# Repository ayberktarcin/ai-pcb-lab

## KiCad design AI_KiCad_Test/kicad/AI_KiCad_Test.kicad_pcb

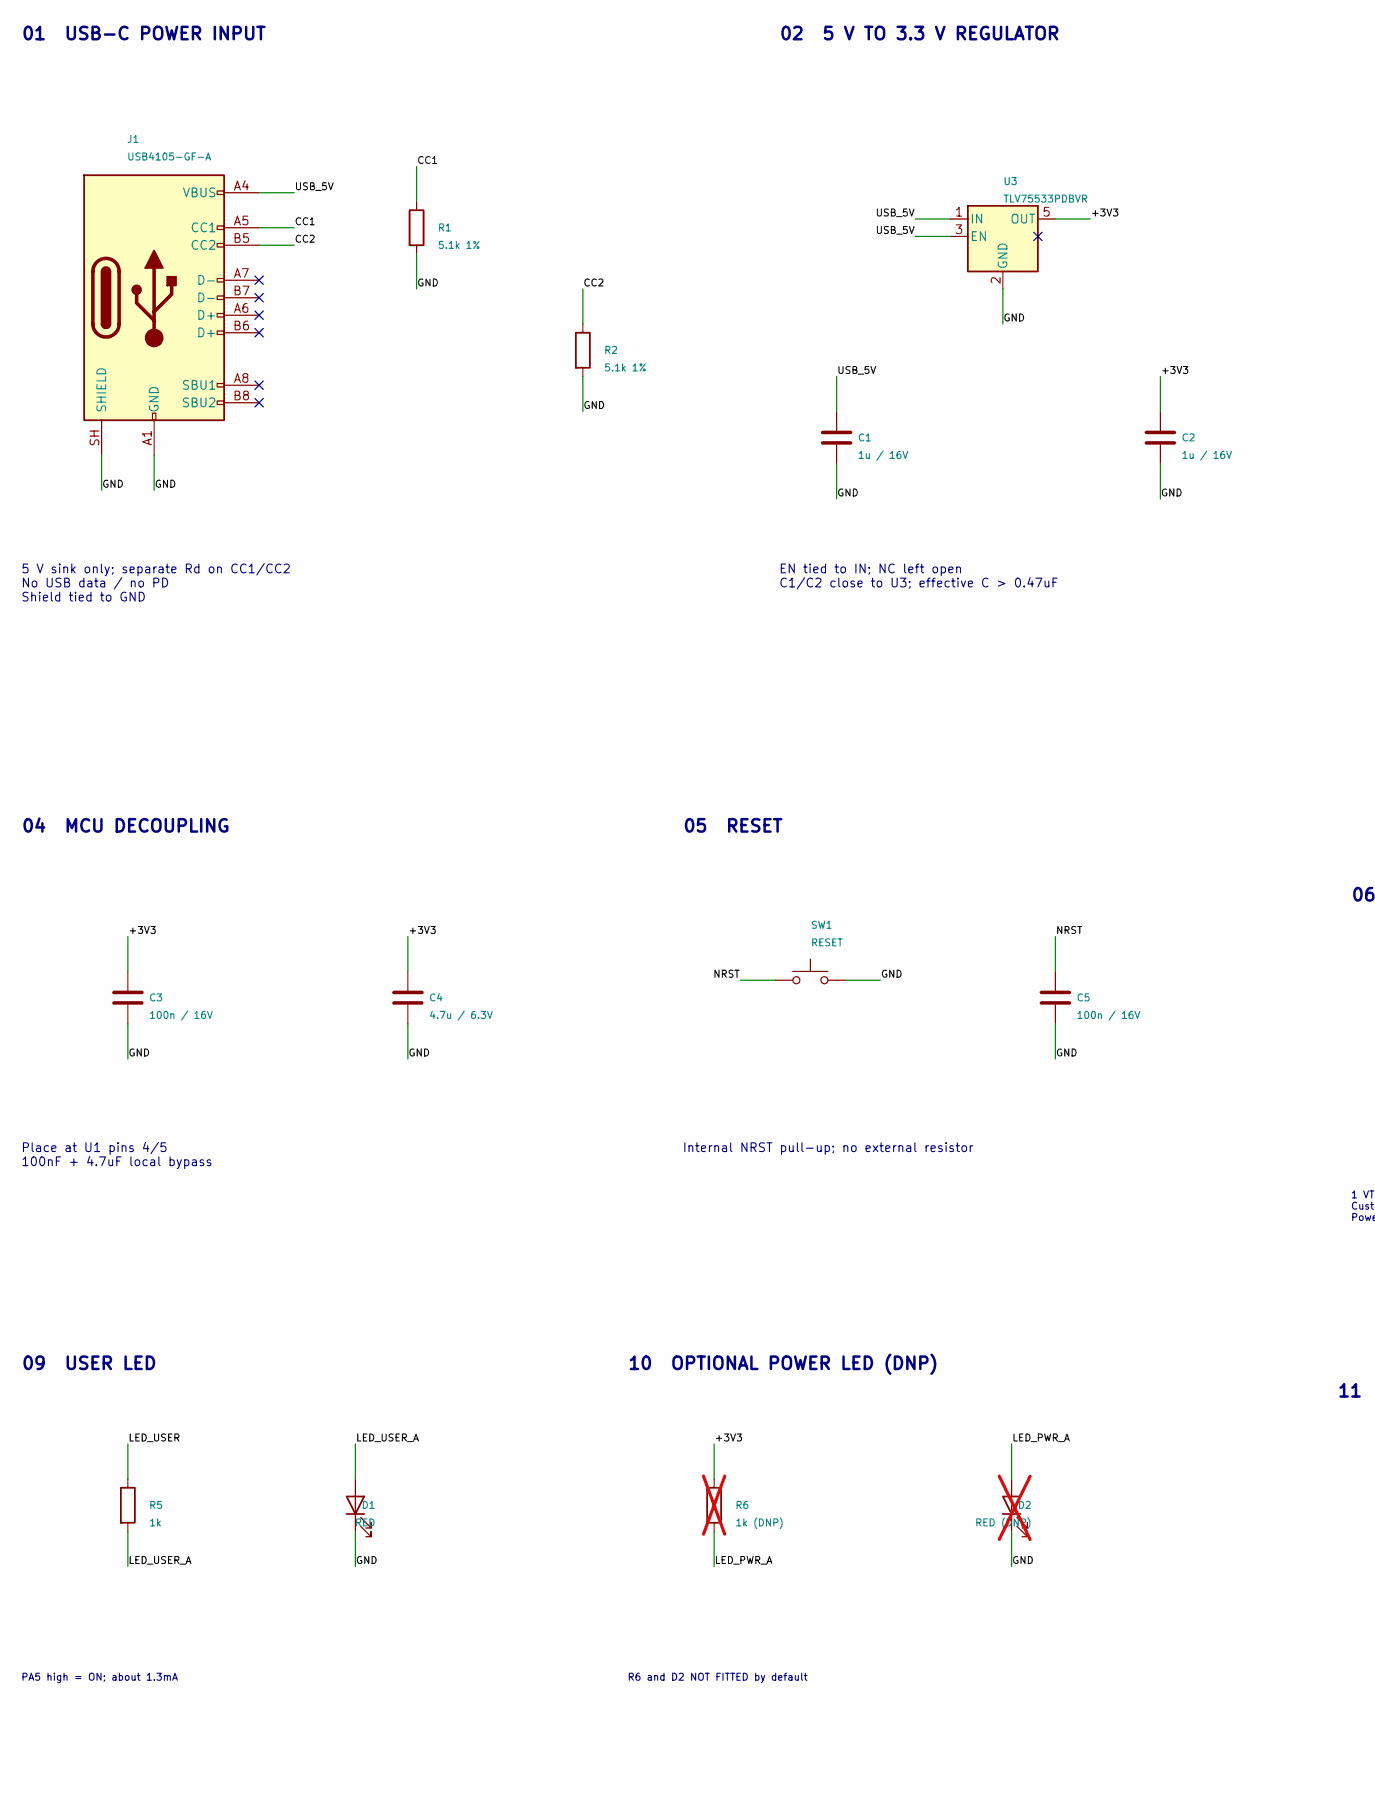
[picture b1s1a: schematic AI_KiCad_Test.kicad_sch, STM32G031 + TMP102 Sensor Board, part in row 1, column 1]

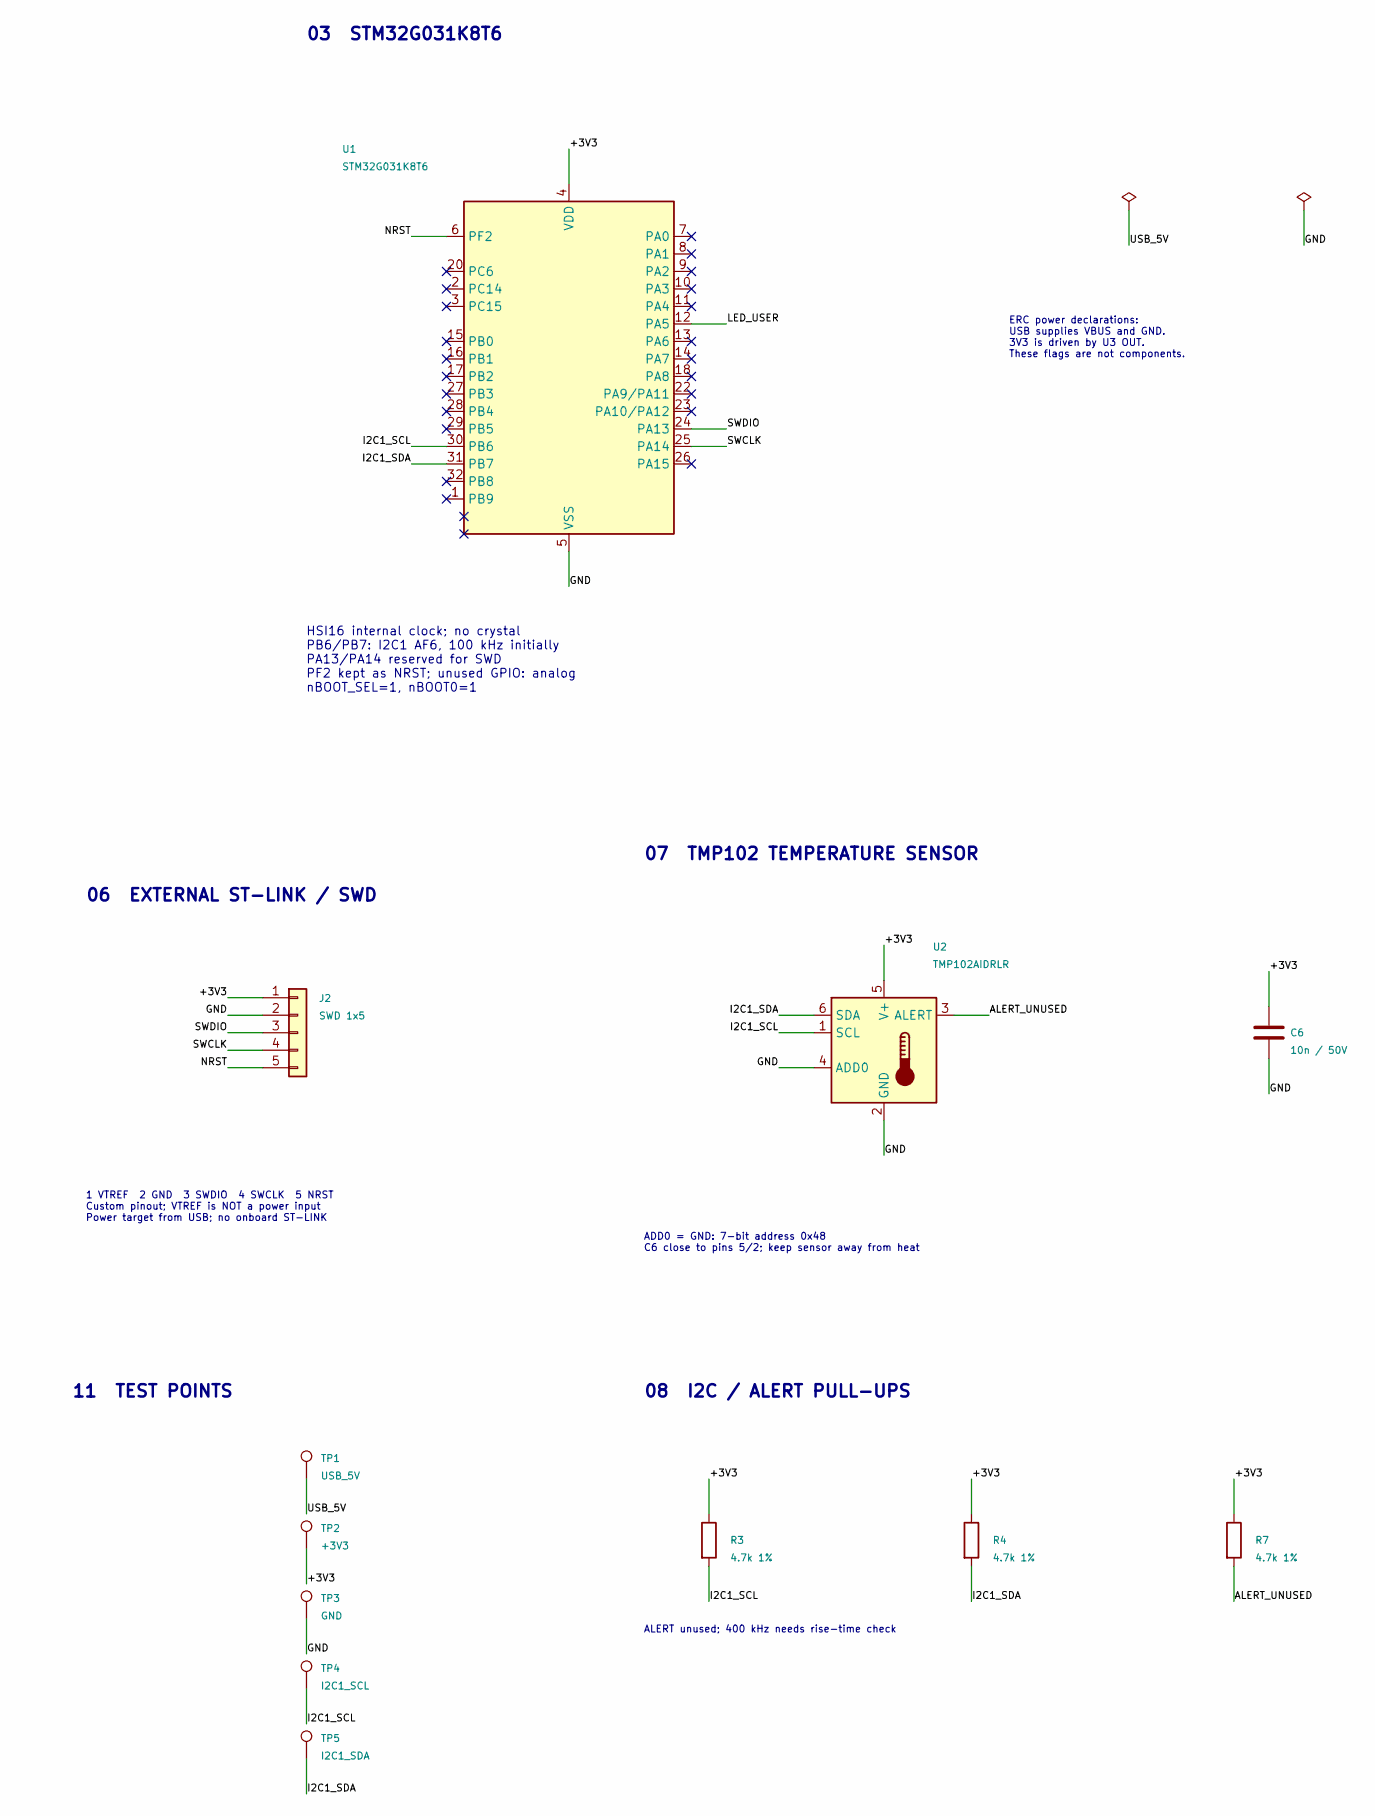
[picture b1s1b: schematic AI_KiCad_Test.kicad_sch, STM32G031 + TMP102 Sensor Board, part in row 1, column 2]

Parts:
C1, C2: 1u / 16V; C_0603_1608Metric; MPN C1608X7R1C105K080AC
C3, C5: 100n / 16V; C_0603_1608Metric; MPN GRM188R71C104KA01D
C4: 4.7u / 6.3V; C_0603_1608Metric; MPN GRM188R60J475KE19D
C6: 10n / 50V; C_0603_1608Metric; MPN C1608X7R1H103K080AA
D1: RED; LED_0603_1608Metric; MPN LTST-C190KRKT
D2: RED (DNP); LED_0603_1608Metric; MPN LTST-C190KRKT; not fitted
J1: USB4105-GF-A; USB_C_Receptacle_GCT_USB4105-xx-A_16P_TopMnt_Horizontal; MPN USB4105-GF-A
J2: SWD 1x5; PinHeader_1x05_P2.54mm_Vertical; MPN TSW-105-07-G-S
R1, R2: 5.1k 1%; R_0603_1608Metric; MPN RC0603FR-075K1L
R3, R4, R7: 4.7k 1%; R_0603_1608Metric; MPN RC0603FR-074K7L
R5: 1k; R_0603_1608Metric; MPN RC0603FR-071KL
R6: 1k (DNP); R_0603_1608Metric; MPN RC0603FR-071KL; not fitted
SW1: RESET; SW_Tactile_SPST_NO_Straight_CK_PTS636Sx25SMTRLFS; MPN PTS636 SK25 SMTR LFS
TP1: USB_5V; TestPoint_Pad_D1.5mm; MPN USB_5V
TP2: +3V3; TestPoint_Pad_D1.5mm; MPN +3V3
TP3: GND; TestPoint_Pad_D1.5mm; MPN GND
TP4: I2C1_SCL; TestPoint_Pad_D1.5mm; MPN I2C1_SCL
TP5: I2C1_SDA; TestPoint_Pad_D1.5mm; MPN I2C1_SDA
U1: STM32G031K8T6; LQFP-32_7x7mm_P0.8mm; MPN STM32G031K8T6
U2: TMP102AIDRLR; SOT-563; MPN TMP102AIDRLR
U3: TLV75533PDBVR; SOT-23-5; MPN TLV75533PDBVR

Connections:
/+3V3: C2.1, C3.1, C4.1, C6.1, J2.1, R3.1, R4.1, R6.1, R7.1, TP2.1 (1_1), U1.4 (VDD), U2.5 (V+), U3.5 (OUT)
/ALERT_UNUSED: R7.2, U2.3 (ALERT)
/CC1: J1.A5 (CC1), R1.1
/CC2: J1.B5 (CC2), R2.1
/GND: C1.2, C2.2, C3.2, C4.2, C5.2, C6.2, D1.1 (K), D2.1 (K), J1.A1 (GND), J1.A12 (GND), J1.B1 (GND), J1.B12 (GND), J1.SH (SHIELD), J2.2, R1.2, R2.2, SW1.2, TP3.1 (1_1), U1.5 (VSS), U2.2 (GND), U2.4 (ADD0), U3.2 (GND)
/I2C1_SCL: R3.2, TP4.1 (1_1), U1.30 (PB6), U2.1 (SCL)
/I2C1_SDA: R4.2, TP5.1 (1_1), U1.31 (PB7), U2.6 (SDA)
/LED_PWR_A: D2.2 (A), R6.2
/LED_USER: R5.1, U1.12 (PA5)
/LED_USER_A: D1.2 (A), R5.2
/NRST: C5.1, J2.5, SW1.1, U1.6 (PF2)
/SWCLK: J2.4, U1.25 (PA14)
/SWDIO: J2.3, U1.24 (PA13)
/USB_5V: C1.1, J1.A4 (VBUS), J1.A9 (VBUS), J1.B4 (VBUS), J1.B9 (VBUS), TP1.1 (1_1), U3.1 (IN), U3.3 (EN)

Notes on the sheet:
ALERT unused; 400 kHz needs rise-time check
08 I2C / ALERT PULL-UPS
09 USER LED
PA5 high = ON; about 1.3mA
02 5 V TO 3.3 V REGULATOR
01 USB-C POWER INPUT
5 V sink only; separate Rd on CC1/CC2 No USB data / no PD Shield tied to GND
10 OPTIONAL POWER LED (DNP)
1 VTREF 2 GND 3 SWDIO 4 SWCLK 5 NRST Custom pinout; VTREF is NOT a power input Power target from USB; no onboard ST-LINK
ERC power declarations: USB supplies VBUS and GND. 3V3 is driven by U3 OUT. These flags are not components.
EN tied to IN; NC left open C1/C2 close to U3; effective C > 0.47uF
11 TEST POINTS
R6 and D2 NOT FITTED by default
03 STM32G031K8T6
Place at U1 pins 4/5 100nF + 4.7uF local bypass
ADD0 = GND: 7-bit address 0x48 C6 close to pins 5/2; keep sensor away from heat
04 MCU DECOUPLING
05 RESET
Internal NRST pull-up; no external resistor
06 EXTERNAL ST-LINK / SWD
HSI16 internal clock; no crystal PB6/PB7: I2C1 AF6, 100 kHz initially PA13/PA14 reserved for SWD PF2 kept as NRST; unused GPIO: analog nBOOT_SEL=1, nBOOT0=1
07 TMP102 TEMPERATURE SENSOR

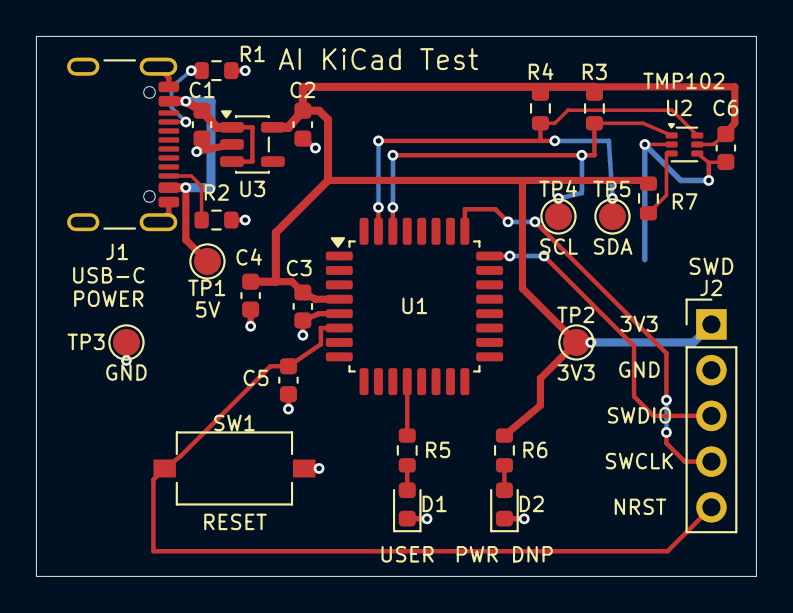
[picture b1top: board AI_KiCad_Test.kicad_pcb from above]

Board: 2 copper layers, 40.0 x 30.0 mm, 26 parts (0 on the bottom side), 14 nets.
